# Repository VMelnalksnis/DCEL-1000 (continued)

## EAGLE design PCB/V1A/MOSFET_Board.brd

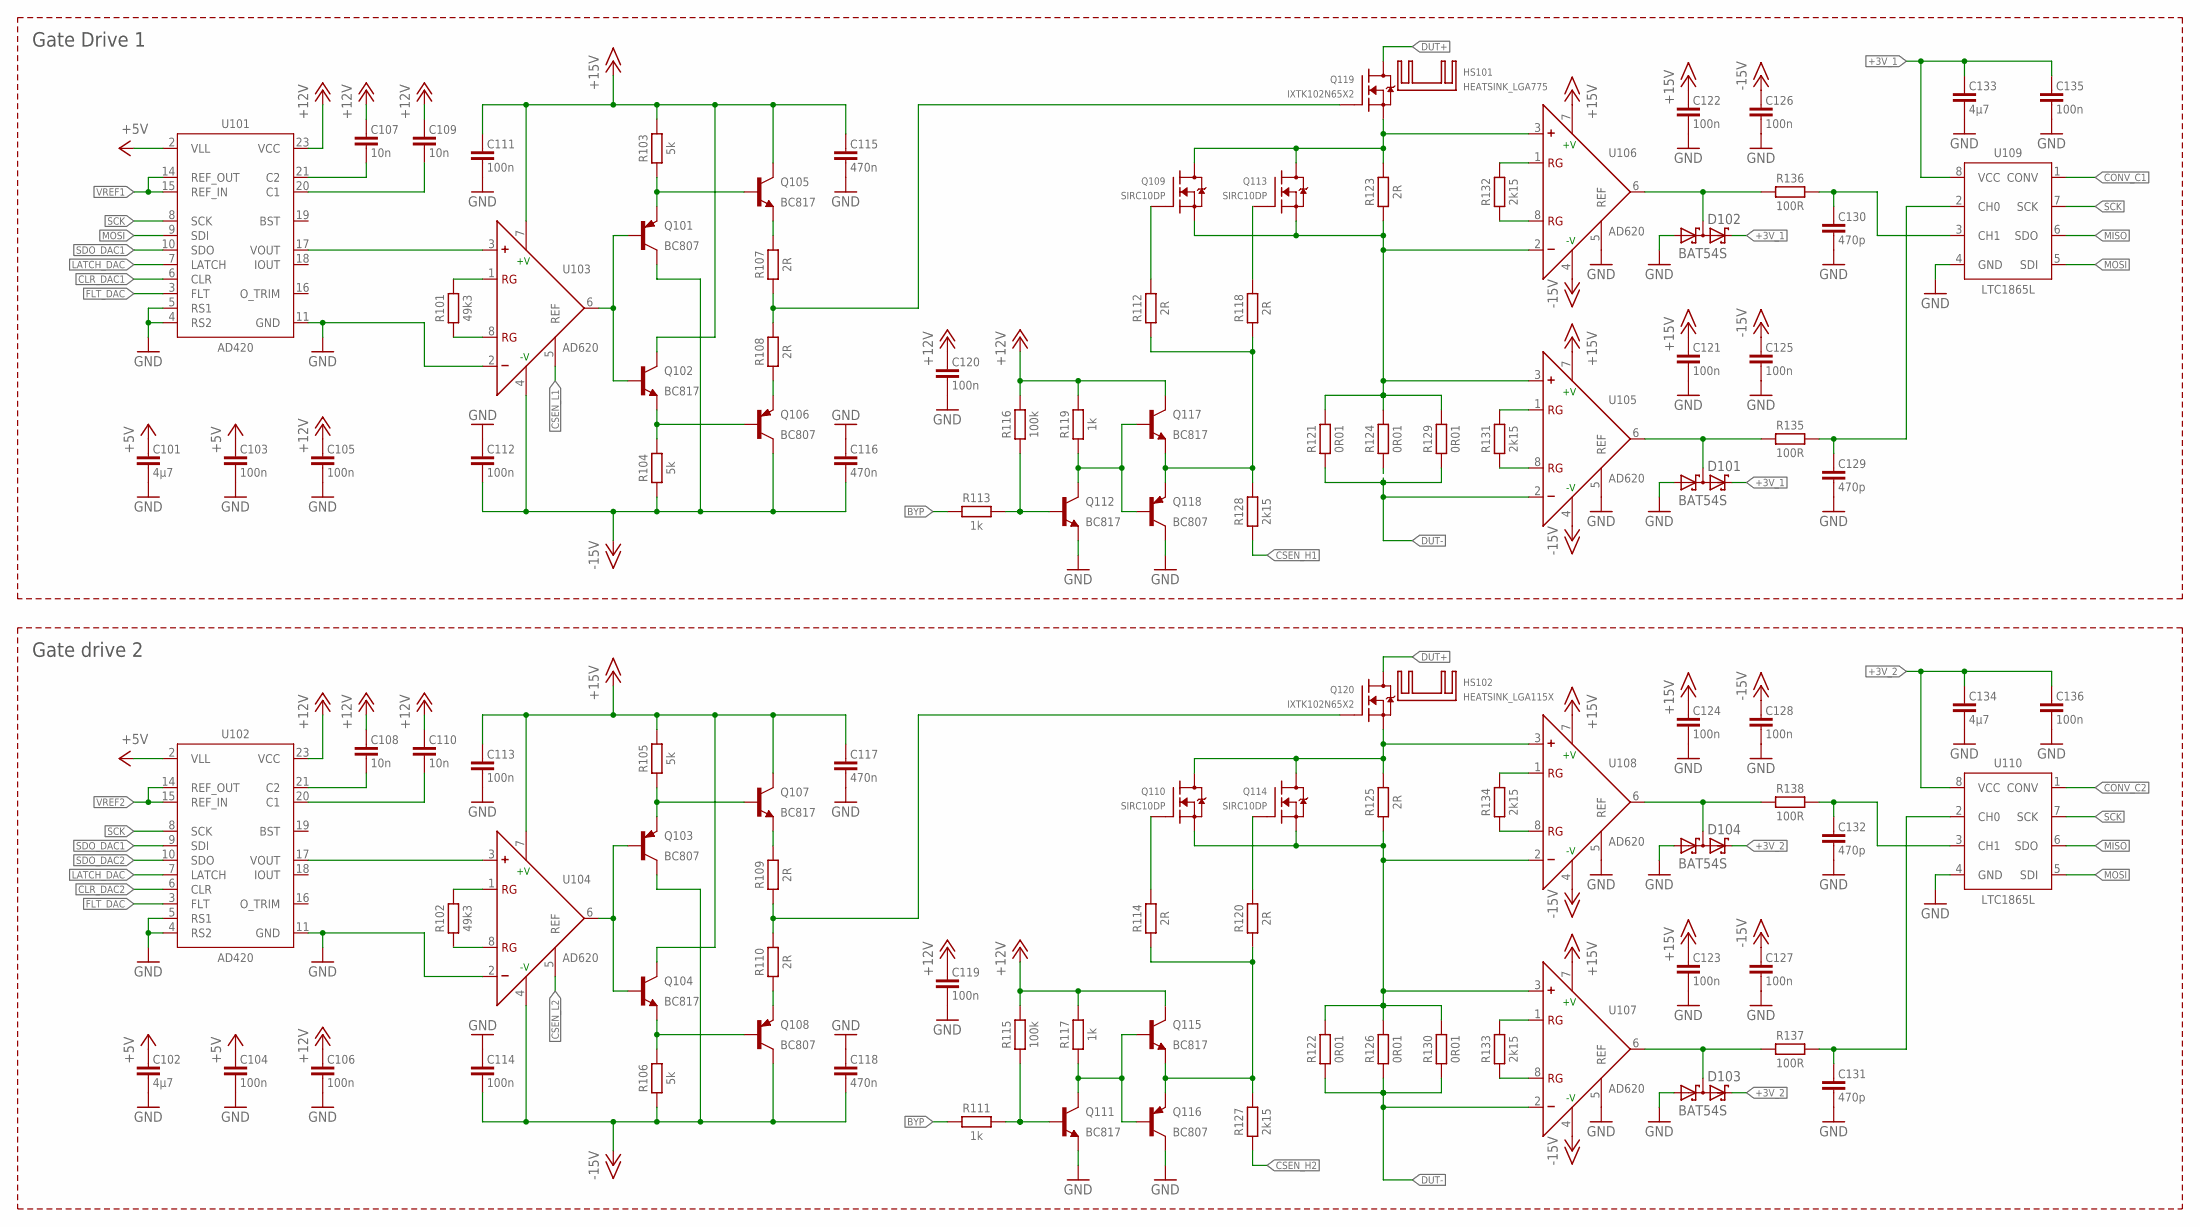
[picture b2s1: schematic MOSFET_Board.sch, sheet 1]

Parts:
C101, C102, C133, C134: 4µ7; CAPC3216
C103, C104, C105, C106, C111, C112, C113, C114, C119, C120, C121, C122, C123, C124, C125, C126, C127, C128, C135, C136: 100n; CAPC1608
C107, C108, C109, C110: 10n; CAPC2012
C115, C116, C117, C118: 470n; CAPC1608
C129, C130, C131, C132: 470p; CAPC1608
D101, D102, D103, D104: BAT54S; SOT23
HS101: HEATSINK_LGA775; D95263-001
HS102: HEATSINK_LGA115X; E97378-001
Q101, Q103, Q106, Q108, Q116, Q118: BC807; SOT23
Q102, Q104, Q105, Q107, Q111, Q112, Q115, Q117: BC817; SOT23
Q109, Q110, Q113, Q114: SIRC10DP; POWERPAK-SO-8
Q119, Q120: IXTK102N65X2; TO-264P-H-PADUP
R101, R102: 49k3; RESC1608
R103, R104, R105, R106: 5k; RESC1608
R107, R108, R109, R110, R112, R114, R118, R120, R123, R125: 2R; RESC3216
R111, R113, R117, R119: 1k; RESC1608
R115, R116: 100k; RESC1608
R121, R122, R124, R126, R129, R130: 0R01; RESC6332
R127, R128, R131, R132, R133, R134: 2k15; RESC2012
R135, R136, R137, R138: 100R; RESC1608
U101, U102: AD420; SO24W
U103, U104, U105, U106, U107, U108: AD620; SO8
U109, U110: LTC1865L; SO8

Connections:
+3V_1: C133.1, C135.1, D101.2 (C2), D102.2 (C2), U109.8 (VCC); also elsewhere on the board
+3V_2: C134.1, C136.1, D103.2 (C2), D104.2 (C2), U110.8 (VCC); also elsewhere on the board
+5V: C101.1, C102.1, C103.1, C104.1, U101.2 (VLL), U102.2 (VLL); also elsewhere on the board
+12V: C105.1, C106.1, C107.1, C108.1, C109.1, C110.1, C119.1, C120.1, Q115.3 (C), Q117.3 (C), R115.2, R116.2, R117.2, R119.2, U101.23 (VCC), U102.23 (VCC); also elsewhere on the board
+15V: C111.1, C113.1, C115.1, C117.1, C121.1, C122.1, C123.1, C124.1, Q102.3 (C), Q104.3 (C), Q105.3 (C), Q107.3 (C), R103.2, R105.2, U103.7 (+V), U104.7 (+V), U105.7 (+V), U106.7 (+V), U107.7 (+V), U108.7 (+V); also elsewhere on the board
-15V: C112.2, C114.2, C116.2, C118.2, C125.1, C126.1, C127.1, C128.1, Q101.3 (C), Q103.3 (C), Q106.3 (C), Q108.3 (C), R104.1, R106.1, U103.4 (-V), U104.4 (-V), U105.4 (-V), U106.4 (-V), U107.4 (-V), U108.4 (-V); also elsewhere on the board
BPY1G1: Q109.4 (G), R112.2
BYP: R111.1, R113.1; also elsewhere on the board
BYP1: Q117.2 (E), Q118.2 (E), R112.1, R118.1, R128.1
BYP1G2: Q113.4 (G), R118.2
BYP2: Q115.2 (E), Q116.2 (E), R114.1, R120.1, R127.2
BYP2G1: Q110.4 (G), R114.2
BYP2G2: Q114.4 (G), R120.2
CLR_DAC1: U101.6 (CLR); also elsewhere on the board
CLR_DAC2: U102.6 (CLR); also elsewhere on the board
CONV_C1: U109.1 (CONV); also elsewhere on the board
CONV_C2: U110.1 (CONV); also elsewhere on the board
CSEN_H1: Q109.1 (S), Q109.2 (S), Q109.3 (S), Q113.1 (S), Q113.2 (S), Q113.3 (S), R121.2, R123.1, R124.2, R128.2, R129.2, U105.3 (+), U106.2 (-)
CSEN_H2: Q110.1 (S), Q110.2 (S), Q110.3 (S), Q114.1 (S), Q114.2 (S), Q114.3 (S), R122.2, R125.1, R126.2, R127.1, R130.2, U107.3 (+), U108.2 (-)
CSEN_L1: Q109.5 (D), Q109.6 (D), Q109.7 (D), Q109.8 (D), Q113.5 (D), Q113.6 (D), Q113.7 (D), Q113.8 (D), Q119.1 (S), R123.2, U103.5 (REF), U106.3 (+)
CSEN_L2: Q110.5 (D), Q110.6 (D), Q110.7 (D), Q110.8 (D), Q114.5 (D), Q114.6 (D), Q114.7 (D), Q114.8 (D), Q120.1 (S), R125.2, U104.5 (REF), U108.3 (+)
DUT+: Q119.2 (D), Q120.2 (D); also elsewhere on the board
DUT-: R121.1, R122.1, R124.1, R126.1, R129.1, R130.1, U105.2 (-), U107.2 (-); also elsewhere on the board
FLT_DAC: U101.3 (FLT), U102.3 (FLT); also elsewhere on the board
GND: C101.2, C102.2, C103.2, C104.2, C105.2, C106.2, C111.2, C112.1, C113.2, C114.1, C115.2, C116.1, C117.2, C118.1, C119.2, C120.2, C121.2, C122.2, C123.2, C124.2, C125.2, C126.2, C127.2, C128.2, C129.2, C130.2, C131.2, C132.2, C133.2, C134.2, C135.2, C136.2, D101.1 (A1), D102.1 (A1), D103.1 (A1), D104.1 (A1), Q111.2 (E), Q112.2 (E), Q116.3 (C), Q118.3 (C), U101.4 (RS2), U101.5 (RS1), U101.11 (GND), U102.4 (RS2), U102.5 (RS1), U102.11 (GND), U103.2 (-), U104.2 (-), U105.5 (REF), U106.5 (REF), U107.5 (REF), U108.5 (REF), U109.4 (GND), U110.4 (GND); also elsewhere on the board
HIGHC1: C129.1, R135.2, U109.2 (CH0)
HIGHC2: C131.1, R137.2, U110.2 (CH0)
LATCH_DAC: U101.7 (LATCH), U102.7 (LATCH); also elsewhere on the board
LGATE_1: Q119.3 (G), R107.1, R108.2
LGATE_2: Q120.3 (G), R109.1, R110.2
LOWC1: C130.1, R136.2, U109.3 (CH1)
LOWC2: C132.1, R138.2, U110.3 (CH1)
MISO: U109.6 (SDO), U110.6 (SDO); also elsewhere on the board
MOSI: U101.9 (SDI), U109.5 (SDI), U110.5 (SDI); also elsewhere on the board
unnamed: Q101.2 (E), Q105.1 (B), R103.1
unnamed: R101.2, U103.1 (RG)
unnamed: C107.2, U101.21 (C2)
unnamed: C109.2, U101.20 (C1)
unnamed: Q112.3 (C), Q117.1 (B), Q118.1 (B), R119.1
unnamed: R101.1, U103.8 (RG)
unnamed: D101.3 (C1A2), R135.1, U105.6 (OUT)
unnamed: Q112.1 (B), R113.2, R116.1
unnamed: U101.17 (VOUT), U103.3 (+)
unnamed: Q106.2 (E), R108.1
unnamed: Q103.2 (E), Q107.1 (B), R105.1
unnamed: Q105.2 (E), R107.2
unnamed: Q108.2 (E), R110.1
unnamed: Q107.2 (E), R109.2
unnamed: D102.3 (C1A2), R136.1, U106.6 (OUT)
unnamed: Q111.3 (C), Q115.1 (B), Q116.1 (B), R117.1
unnamed: Q111.1 (B), R111.2, R115.1
unnamed: C108.2, U102.21 (C2)
unnamed: C110.2, U102.20 (C1)
unnamed: Q103.1 (B), Q104.1 (B), U104.6 (OUT)
unnamed: Q104.2 (E), Q108.1 (B), R106.2
unnamed: R102.2, U104.1 (RG)
unnamed: R102.1, U104.8 (RG)
unnamed: U102.17 (VOUT), U104.3 (+)
unnamed: D103.3 (C1A2), R137.1, U107.6 (OUT)
unnamed: D104.3 (C1A2), R138.1, U108.6 (OUT)
unnamed: Q101.1 (B), Q102.1 (B), U103.6 (OUT)
unnamed: Q102.2 (E), Q106.1 (B), R104.2
RG1_L1: R133.2, U107.1 (RG)
RG1_L2: R134.2, U108.1 (RG)
RG1_L3: R131.2, U105.1 (RG)
RG1_L4: R132.2, U106.1 (RG)
RG2_L1: R133.1, U107.8 (RG)
RG2_L2: R134.1, U108.8 (RG)
RG2_L3: R131.1, U105.8 (RG)
RG2_L4: R132.1, U106.8 (RG)
SCK: U101.8 (SCK), U102.8 (SCK), U109.7 (SCK), U110.7 (SCK); also elsewhere on the board
SDO_DAC1: U101.10 (SDO), U102.9 (SDI)
SDO_DAC2: U102.10 (SDO)
VREF1: U101.14 (REF_OUT), U101.15 (REF_IN); also elsewhere on the board
VREF2: U102.14 (REF_OUT), U102.15 (REF_IN); also elsewhere on the board

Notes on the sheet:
Gate Drive 1
Gate drive 2

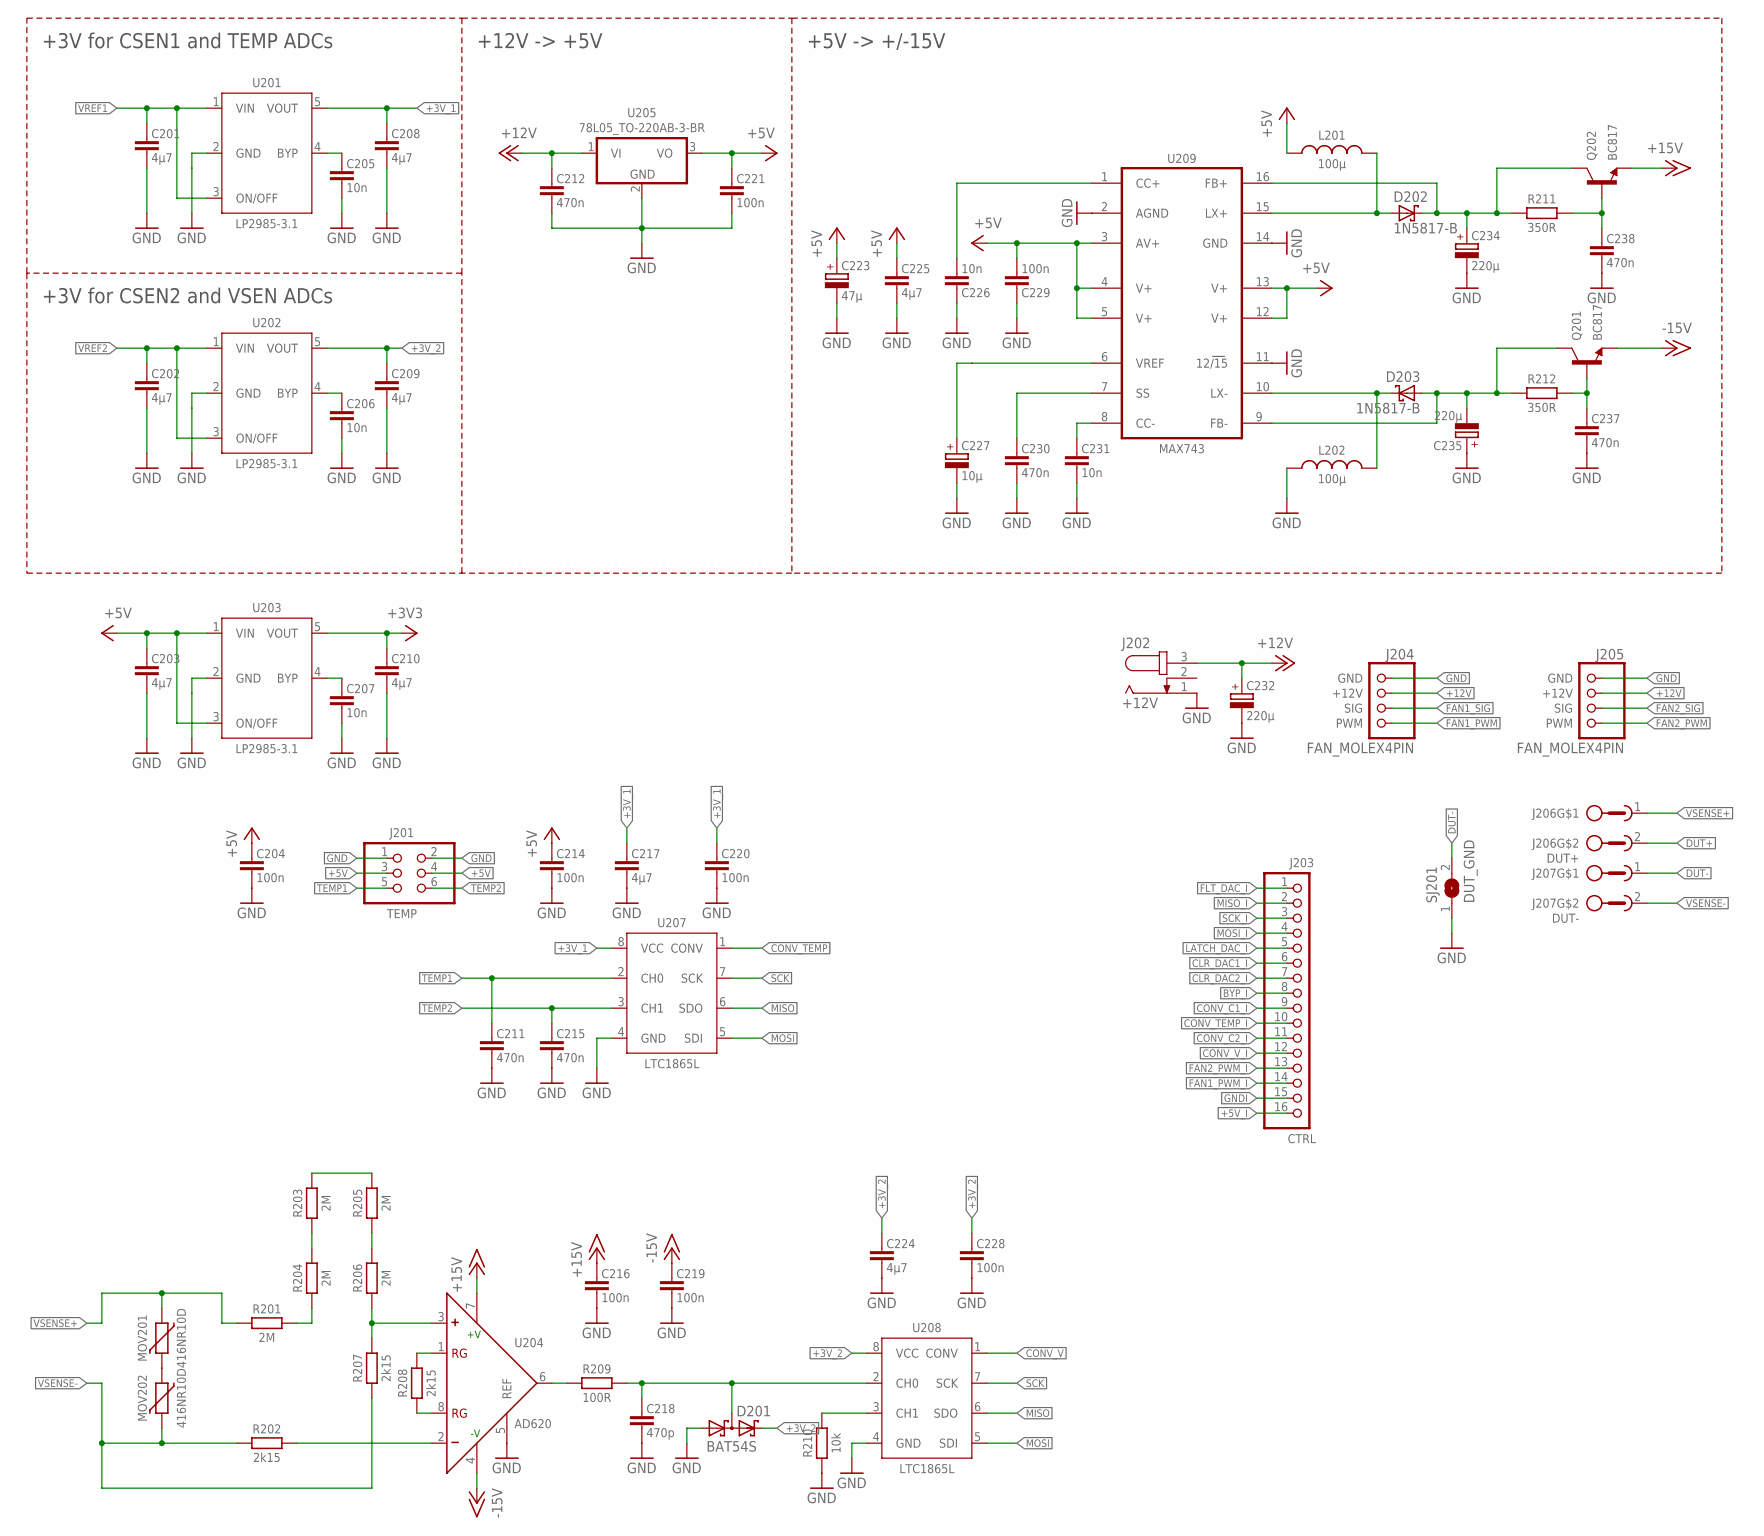
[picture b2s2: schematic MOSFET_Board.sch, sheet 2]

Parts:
C201, C202, C203, C208, C209, C210, C217, C224, C225: 4µ7; CAPC3216
C204, C214, C216, C219, C220, C221, C228, C229: 100n; CAPC1608
C205, C206, C207, C226, C231: 10n; CAPC2012
C211, C212, C215, C230, C237, C238: 470n; CAPC1608
C218: 470p; CAPC1608
C223: 47µ; CAPCP7343
C227: 10µ; CAPCP6032
C232, C234, C235: 220µ; CAPPRD500W60D1000H
D201: BAT54S; SOT23
D202, D203: 1N5817-B; DO41-7.6
J201: TEMP; HEAD_MALE_2X3
J202: +12V; SPC4078
J203: CTRL; HEAD_MALE_1X16
J204, J205: FAN_MOLEX4PIN; MOLEX_47053-1000
J206: DUT+; AMPHENOL-12-762_2
J207: DUT-; AMPHENOL-12-762_2
L201, L202: 100µ; MSS1260
MOV201, MOV202: 416NR10D; DISK_9.5MM
Q201, Q202: BC817; SOT23
R201, R203, R204, R205, R206: 2M; RESC3216
R202, R207, R208: 2k15; RESC2012
R209: 100R; RESC1608
R210: 10k; RESC1608
R211, R212: 350R; RESC1608
SJ201: DUT_GND; SJW
U201, U202, U203: LP2985-3.1; SOT23-5L
U204: AD620; SO8
U205: 78L05_TO-220AB-3-BR; TO-220AB-3-BR
U207, U208: LTC1865L; SO8
U209: MAX743; SO16W

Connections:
+3V3: C210.1, U203.5 (VOUT); also elsewhere on the board
+3V_1: C208.1, C217.1, C220.1, U201.5 (VOUT), U207.8 (VCC); also elsewhere on the board
+3V_2: C209.1, C224.1, C228.1, D201.2 (C2), U202.5 (VOUT), U208.8 (VCC); also elsewhere on the board
+5V: C203.1, C204.1, C214.1, C221.1, C223.+, C225.1, C229.2, J201.3, J201.4, L201.1, U203.1 (VIN), U203.3 (ON/OFF), U205.3 (VO), U209.3 (AV+), U209.4 (V+), U209.5 (V+), U209.12 (V+), U209.13 (V+); also elsewhere on the board
+5V_I: J203.16; also elsewhere on the board
+12V: C212.1, C232.+, J202.3, J204.2 (+12V), J205.2 (+12V), U205.1 (VI); also elsewhere on the board
+15V: C216.1, Q202.2 (E), U204.7 (+V); also elsewhere on the board
-15V: C219.1, Q201.2 (E), U204.4 (-V); also elsewhere on the board
BYP_I: J203.8; also elsewhere on the board
CLR_DAC1_I: J203.6; also elsewhere on the board
CLR_DAC2_I: J203.7; also elsewhere on the board
CONV_C1_I: J203.9; also elsewhere on the board
CONV_C2_I: J203.11; also elsewhere on the board
CONV_TEMP: U207.1 (CONV); also elsewhere on the board
CONV_TEMP_I: J203.10; also elsewhere on the board
CONV_V: U208.1 (CONV); also elsewhere on the board
CONV_V_I: J203.12; also elsewhere on the board
DUT+: J206.2; also elsewhere on the board
DUT-: J207.1, SJ201.2; also elsewhere on the board
FAN1_PWM: J204.4 (PWM); also elsewhere on the board
FAN1_PWM_I: J203.14; also elsewhere on the board
FAN1_SIG: J204.3 (SIG)
FAN2_PWM: J205.4 (PWM); also elsewhere on the board
FAN2_PWM_I: J203.13; also elsewhere on the board
FAN2_SIG: J205.3 (SIG)
FLT_DAC_I: J203.1; also elsewhere on the board
GND: C201.2, C202.2, C203.2, C204.2, C205.2, C206.2, C207.2, C208.2, C209.2, C210.2, C211.2, C212.2, C214.2, C215.2, C216.2, C217.2, C218.2, C219.2, C220.2, C221.2, C223.-, C224.2, C225.2, C226.1, C227.-, C228.2, C229.1, C230.2, C231.2, C232.-, C234.-, C235.+, C237.2, C238.2, D201.1 (A1), J201.1, J201.2, J202.1, J204.1 (GND), J205.1 (GND), L202.2, R210.1, SJ201.1, U201.2 (GND), U202.2 (GND), U203.2 (GND), U204.5 (REF), U205.2 (GND), U207.4 (GND), U208.4 (GND), U209.2 (AGND), U209.11 (12/15), U209.14 (GND); also elsewhere on the board
GNDI: J203.15; also elsewhere on the board
LATCH_DAC_I: J203.5; also elsewhere on the board
MISO: U207.6 (SDO), U208.6 (SDO); also elsewhere on the board
MISO_I: J203.2; also elsewhere on the board
MOSI: U207.5 (SDI), U208.5 (SDI); also elsewhere on the board
MOSI_I: J203.4; also elsewhere on the board
unnamed: C205.1, U201.4 (BYP)
unnamed: R209.1, U204.6 (OUT)
unnamed: R205.1, R206.2
unnamed: R203.2, R205.2
unnamed: R203.1, R204.2
unnamed: MOV201.2, MOV202.1
unnamed: R206.1, R207.2, U204.3 (+)
unnamed: C218.1, D201.3 (C1A2), R209.2, U208.2 (CH0)
unnamed: C234.+, D202.C, Q202.3 (C), R211.1, U209.16 (FB+)
unnamed: R201.2, R204.1
unnamed: C231.1, U209.8 (CC-)
unnamed: C230.1, U209.7 (SS)
unnamed: R202.2, U204.2 (-)
unnamed: C226.2, U209.1 (CC+)
unnamed: D202.A, L201.2, U209.15 (LX+)
unnamed: D203.C, L202.1, U209.10 (LX-)
unnamed: R210.2, U208.3 (CH1)
unnamed: C206.1, U202.4 (BYP)
unnamed: C238.1, Q202.1 (B), R211.2
unnamed: C235.-, D203.A, Q201.3 (C), R212.1, U209.9 (FB-)
unnamed: C237.1, Q201.1 (B), R212.2
unnamed: C207.1, U203.4 (BYP)
RG1_H6: R208.2, U204.1 (RG)
RG2_H6: R208.1, U204.8 (RG)
SCK: U207.7 (SCK), U208.7 (SCK); also elsewhere on the board
SCK_I: J203.3; also elsewhere on the board
TEMP1: C211.1, J201.5, U207.2 (CH0)
TEMP2: C215.1, J201.6, U207.3 (CH1)
VREF1: C201.1, U201.1 (VIN), U201.3 (ON/OFF); also elsewhere on the board
VREF2: C202.1, U202.1 (VIN), U202.3 (ON/OFF); also elsewhere on the board
VREF_MAX743: C227.+, U209.6 (VREF)
VSENSE+: J206.1, MOV201.1, R201.1
VSENSE-: J207.2, MOV202.2, R202.1, R207.1

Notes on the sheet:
+3V for CSEN1 and TEMP ADCs
+3V for CSEN2 and VSEN ADCs
+5V -> +/-15V
+12V -> +5V

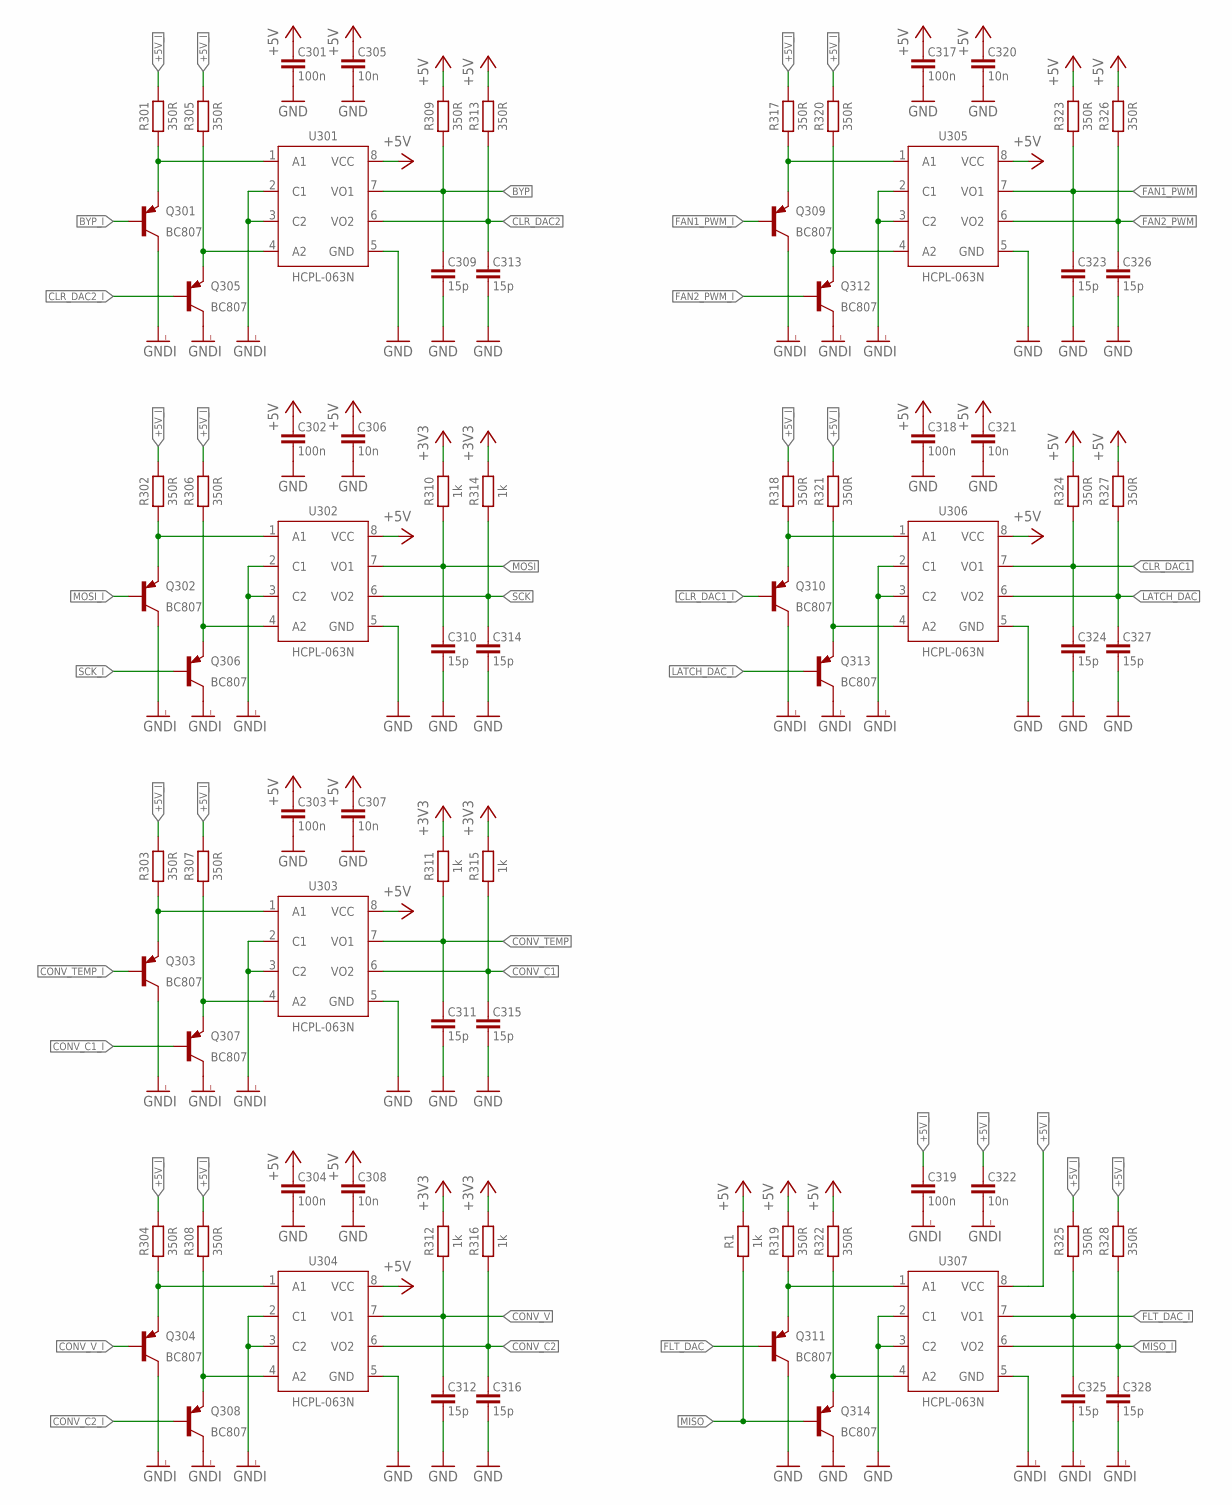
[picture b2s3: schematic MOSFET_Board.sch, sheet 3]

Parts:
C301, C302, C303, C304, C317, C318, C319: 100n; CAPC1608
C305, C306, C307, C308, C320, C321, C322: 10n; CAPC1608
C309, C310, C311, C312, C313, C314, C315, C316, C323, C324, C325, C326, C327, C328: 15p; CAPC1608
Q301, Q302, Q303, Q304, Q305, Q306, Q307, Q308, Q309, Q310, Q311, Q312, Q313, Q314: BC807; SOT23
R1, R310, R311, R312, R314, R315, R316: 1k; RESC1608
R301, R302, R303, R304, R305, R306, R307, R308, R309, R313, R317, R318, R319, R320, R321, R322, R323, R324, R325, R326, R327, R328: 350R; RESC1608
U301, U302, U303, U304, U305, U306, U307: HCPL-063N; SO8

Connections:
+3V3: R310.2, R311.2, R312.2, R314.2, R315.2, R316.2; also elsewhere on the board
+5V: C301.1, C302.1, C303.1, C304.1, C305.1, C306.1, C307.1, C308.1, C317.1, C318.1, C320.1, C321.1, R1.2, R309.2, R313.2, R319.2, R322.2, R323.2, R324.2, R326.2, R327.2, U301.8 (VCC), U302.8 (VCC), U303.8 (VCC), U304.8 (VCC), U305.8 (VCC), U306.8 (VCC); also elsewhere on the board
+5V_I: C319.1, C322.1, R301.2, R302.2, R303.2, R304.2, R305.2, R306.2, R307.2, R308.2, R317.2, R318.2, R320.2, R321.2, R325.2, R328.2, U307.8 (VCC); also elsewhere on the board
BYP: C309.1, R309.1, U301.7 (VO1); also elsewhere on the board
BYP_I: Q301.1 (B); also elsewhere on the board
CLR_DAC1: C324.1, R324.1, U306.7 (VO1); also elsewhere on the board
CLR_DAC1_I: Q310.1 (B); also elsewhere on the board
CLR_DAC2: C313.1, R313.1, U301.6 (VO2); also elsewhere on the board
CLR_DAC2_I: Q305.1 (B); also elsewhere on the board
CONV_C1: C315.1, R315.1, U303.6 (VO2); also elsewhere on the board
CONV_C1_I: Q307.1 (B); also elsewhere on the board
CONV_C2: C316.1, R316.1, U304.6 (VO2); also elsewhere on the board
CONV_C2_I: Q308.1 (B); also elsewhere on the board
CONV_TEMP: C311.1, R311.1, U303.7 (VO1); also elsewhere on the board
CONV_TEMP_I: Q303.1 (B); also elsewhere on the board
CONV_V: C312.1, R312.1, U304.7 (VO1); also elsewhere on the board
CONV_V_I: Q304.1 (B); also elsewhere on the board
FAN1_PWM: C323.1, R323.1, U305.7 (VO1); also elsewhere on the board
FAN1_PWM_I: Q309.1 (B); also elsewhere on the board
FAN2_PWM: C326.1, R326.1, U305.6 (VO2); also elsewhere on the board
FAN2_PWM_I: Q312.1 (B); also elsewhere on the board
FLT_DAC: Q311.1 (B); also elsewhere on the board
FLT_DAC_I: C325.1, R325.1, U307.7 (VO1); also elsewhere on the board
GND: C301.2, C302.2, C303.2, C304.2, C305.2, C306.2, C307.2, C308.2, C309.2, C310.2, C311.2, C312.2, C313.2, C314.2, C315.2, C316.2, C317.2, C318.2, C320.2, C321.2, C323.2, C324.2, C326.2, C327.2, Q311.3 (C), Q314.3 (C), U301.5 (GND), U302.5 (GND), U303.5 (GND), U304.5 (GND), U305.5 (GND), U306.5 (GND), U307.2 (C1), U307.3 (C2); also elsewhere on the board
GNDI: C319.2, C322.2, C325.2, C328.2, Q301.3 (C), Q302.3 (C), Q303.3 (C), Q304.3 (C), Q305.3 (C), Q306.3 (C), Q307.3 (C), Q308.3 (C), Q309.3 (C), Q310.3 (C), Q312.3 (C), Q313.3 (C), U301.2 (C1), U301.3 (C2), U302.2 (C1), U302.3 (C2), U303.2 (C1), U303.3 (C2), U304.2 (C1), U304.3 (C2), U305.2 (C1), U305.3 (C2), U306.2 (C1), U306.3 (C2), U307.5 (GND); also elsewhere on the board
LATCH_DAC: C327.1, R327.1, U306.6 (VO2); also elsewhere on the board
LATCH_DAC_I: Q313.1 (B); also elsewhere on the board
MISO: Q314.1 (B), R1.1; also elsewhere on the board
MISO_I: C328.1, R328.1, U307.6 (VO2); also elsewhere on the board
MOSI: C310.1, R310.1, U302.7 (VO1); also elsewhere on the board
MOSI_I: Q302.1 (B); also elsewhere on the board
unnamed: Q311.2 (E), R319.1, U307.1 (A1)
unnamed: Q314.2 (E), R322.1, U307.4 (A2)
unnamed: Q304.2 (E), R304.1, U304.1 (A1)
unnamed: Q308.2 (E), R308.1, U304.4 (A2)
unnamed: Q302.2 (E), R302.1, U302.1 (A1)
unnamed: Q306.2 (E), R306.1, U302.4 (A2)
unnamed: Q309.2 (E), R317.1, U305.1 (A1)
unnamed: Q312.2 (E), R320.1, U305.4 (A2)
unnamed: Q301.2 (E), R301.1, U301.1 (A1)
unnamed: Q305.2 (E), R305.1, U301.4 (A2)
unnamed: Q310.2 (E), R318.1, U306.1 (A1)
unnamed: Q313.2 (E), R321.1, U306.4 (A2)
unnamed: Q303.2 (E), R303.1, U303.1 (A1)
unnamed: Q307.2 (E), R307.1, U303.4 (A2)
SCK: C314.1, R314.1, U302.6 (VO2); also elsewhere on the board
SCK_I: Q306.1 (B); also elsewhere on the board

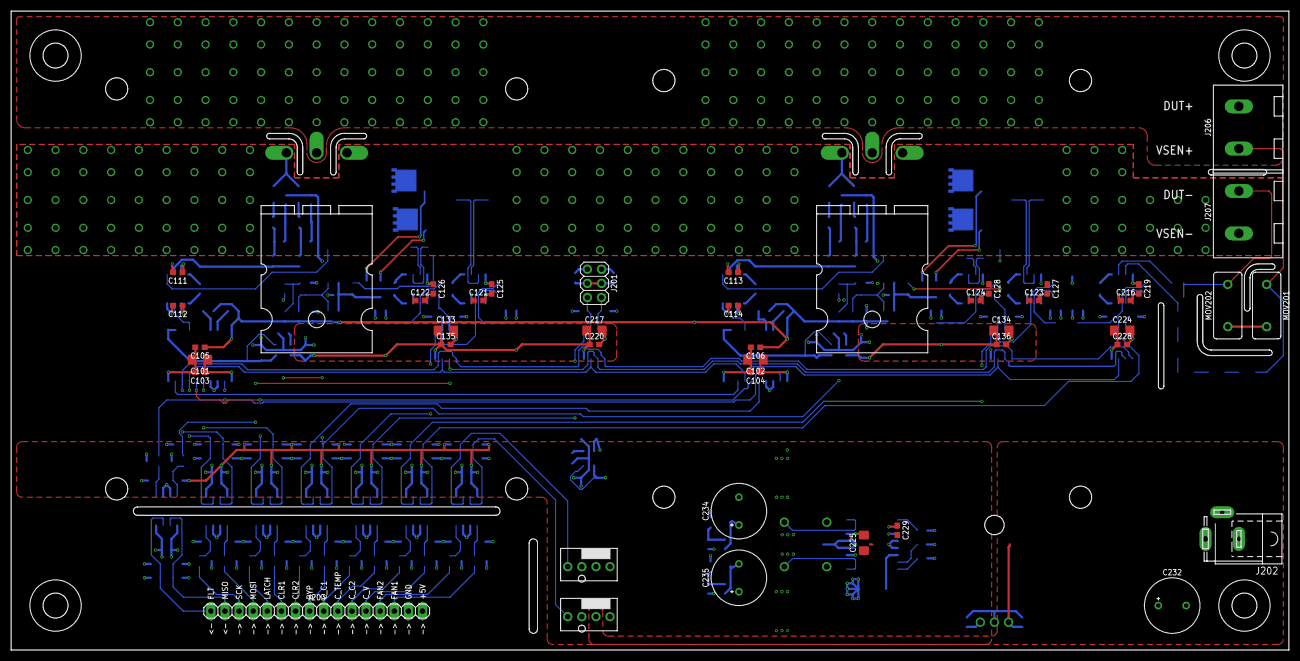
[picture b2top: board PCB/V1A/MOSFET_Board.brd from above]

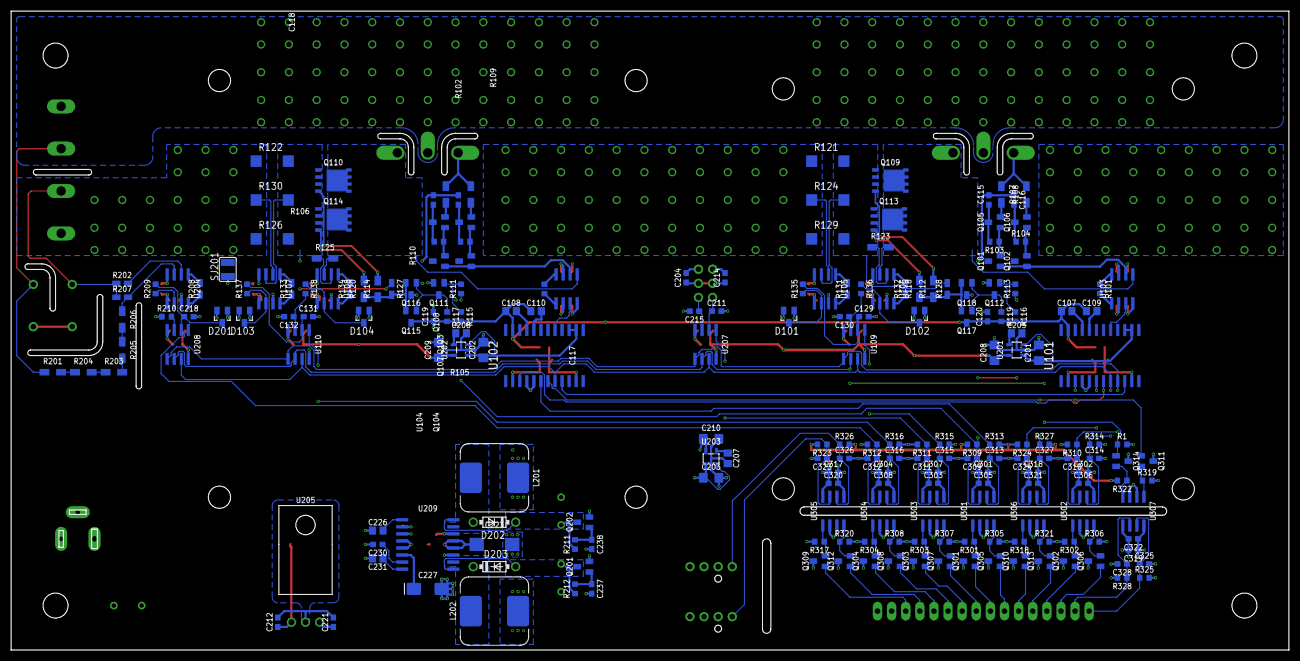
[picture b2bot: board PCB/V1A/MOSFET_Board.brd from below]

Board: 4 copper layers, 230.0 x 115.0 mm, 263 parts (213 on the bottom side), 138 nets.

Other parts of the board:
U$6, U$7, U$8, U$9: M4

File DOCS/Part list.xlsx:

Resistors
Value | Package | Count | Source | Link | Description | Price per | Total
0.01 | 6332 | 6 |  |  |  |  | 0
2 | 3216 | 6 | 610 3-10-2 |  |  |  | 0
16 | THT | 1 |  |  | RC snubber |  | 0
100 | 1608 | 7 | 610 3-13-3 |  |  |  | 0
350 | 1608 | 28 | 610 3-10-5 |  |  |  | 0
1000 | 1608 | 4 | 610 3-13-3 |  |  |  | 0
2150 | 2012 | 10 | 610 3-9-2 |  |  |  | 0
10000 | 1608 | 25 | 610 3-10-5 |  |  |  | 0
100000 | 1608 | 4 | 610 3-13-3 |  |  |  | 0
2000000 | 3216 | 5 | 610 3-25-2 |  |  |  | 0
Capacitors
Value | Package | Count | Source | Link | Description | Price per | Total
1.5E-11 | 1608 | 14 | 610 3-27-4 |  |  |  | 0
4.7000000000000003E-10 | 1608 | 5 | 610 3-13-5 |  |  |  | 0
4.7000000000000003E-10 | THT | 1 |  |  | 5V->5V coupling |  | 0
1E-8 | 2012 | 14 | 610 3-17-3 |  |  |  | 0
9.9999999999999995E-8 | 1608 | 37 |  |  |  |  | 0
1.4999999999999999E-7 | THT | 1 |  |  | RC snubber |  | 0
4.7E-7 | 1608 | 5 | 610 3-13-5 |  |  |  | 0
4.6999999999999999E-6 | 3216 | 8 | 610 3-17-5 |  |  |  | 0
1.0000000000000001E-5 | TANT-C | 2 | 610 3-14-4 |  |  |  | 0
4.6999999999999997E-5 | TANT-D | 1 | 610 3-18-4 |  |  |  | 0
2.2000000000000001E-4 | THT | 3 |  |  |  |  | 0
IC's
Value | Package | Count | Source | Link | Description | Price per | Total
AD420 | SO24W | 2 | 610 3-2-6 |  | 16-bit DAC |  | 0
AD620 | SO8 | 5 | 610 3-2-5 |  | Instrumentation amp |  | 0
HCPL-063N | SO8 | 7 | 610 3-2-6 |  | Dual opto-coupler |  | 0
L7805CV | TO220 | 2 | RTU |  | 5V Linear regulator |  | 0
LM50 | SOT23W | 2 | 610 3-14-1 |  | Temperature sensor |  | 0
LP2985-3.0 | SOT23-5L | 1 | 610 3-18-1 |  | LDO 3V regulator |  | 0
LT1014ISW | SO16W | 2 | RTU |  | Quad opamp |  | 0
LTC1865L | SO8 | 4 | 610 3-2-5 |  | 16-bit dual ADC |  | 0
MAX743WE | SO16W | 1 | 610 3-2-6 |  | 5V to +/-15V regulator |  | 0
Discrete semiconductors
Value | Package | Count | Source | Link | Description | Price per | Total
1N5817-B | DO41-7.6 | 2 | RTU |  |  |  | 0
BAS70-04 | SOT23 | 4 | 610 3-12-1 |  |  |  | 0
BC807-40 | SOT23 | 16 | 610 3-11-1 |  |  |  | 0
BC817-40 | SOT23 | 4 | 610 3-10-1 |  |  |  | 0
IXTK102N65X2 | TO264 | 2 | farnell | lv.farnell.com/ixys-semiconductor/ixtk102n65x2/mosfet-n-ch-650v-102a-to-264p/dp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 |  | 12.88 | 25.76
SiRC10DP | SO8 | 4 | RTU |  |  |  | 0
Connectors
Value | Package | Count | Source | Link | Description | Price per | Total
Barrel Jack |  | 1 | Me |  |  |  | 0
Fan header | 4 pin | 2 |  |  |  |  | 0
Header pins |  | 1 | Me |  |  |  | 0
Screw terminals | 2/7.62 pitch | 2 | digikey | digikey.lv/product-detail/en/amphenol-anytek/T70243500000G/609-3954-ND/2261340 |  | 0.89 | 1.78
The rest
Value | Package | Count | Source | Link | Description | Price per | Total
100µ inductor |  | 2 | farnell | lv.farnell.com/coilcraft/mss1260-104mld/inductor-pwr-100uh-2-1a-20-8mhz/dp/2288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 |  | 1.22 | 2.44
Heatsink | LGA1155/755 | 2 | Me |  |  |  | 0
MOV |  | 4 |  |  |  |  | 0
RFMM-0505S | SIP7 | 1 | digikey | digikey.lv/products/en?keywords=RFMM-0505S | 5V->5V isolated supply | 1.45 | 1.45
Thermal interface |  |  |  |  |  |  | 0
Total: |  | 260 |  |  |  |  | 31.43

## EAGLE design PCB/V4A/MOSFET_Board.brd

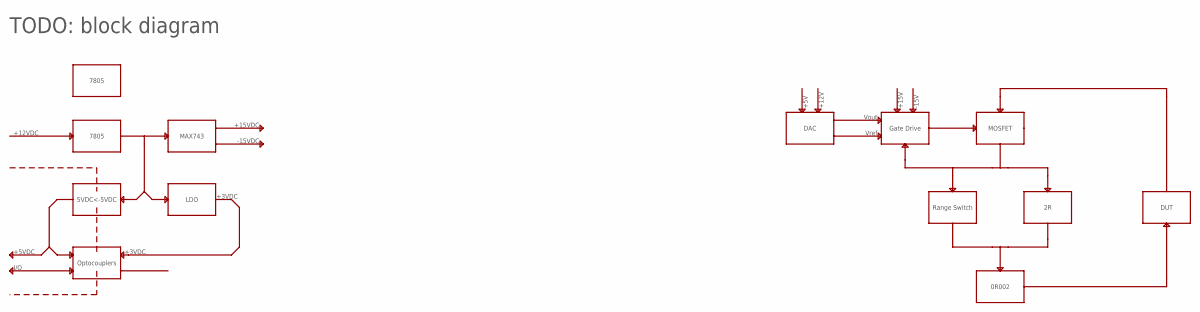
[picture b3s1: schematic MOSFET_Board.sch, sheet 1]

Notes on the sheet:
TODO: block diagram
I/O
Optocouplers
+5VDC
5VDC<-5VDC
7805
+12VDC
MAX743
+15VDC
-15VDC
LDO
+3VDC
DUT
MOSFET
Gate Drive
DAC
0R002
Range Switch
Vout
Vref
+15V
-15V
+5V
+12V
